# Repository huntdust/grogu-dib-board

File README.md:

# grogu-dib-board
 DIB board for Grogu PTL

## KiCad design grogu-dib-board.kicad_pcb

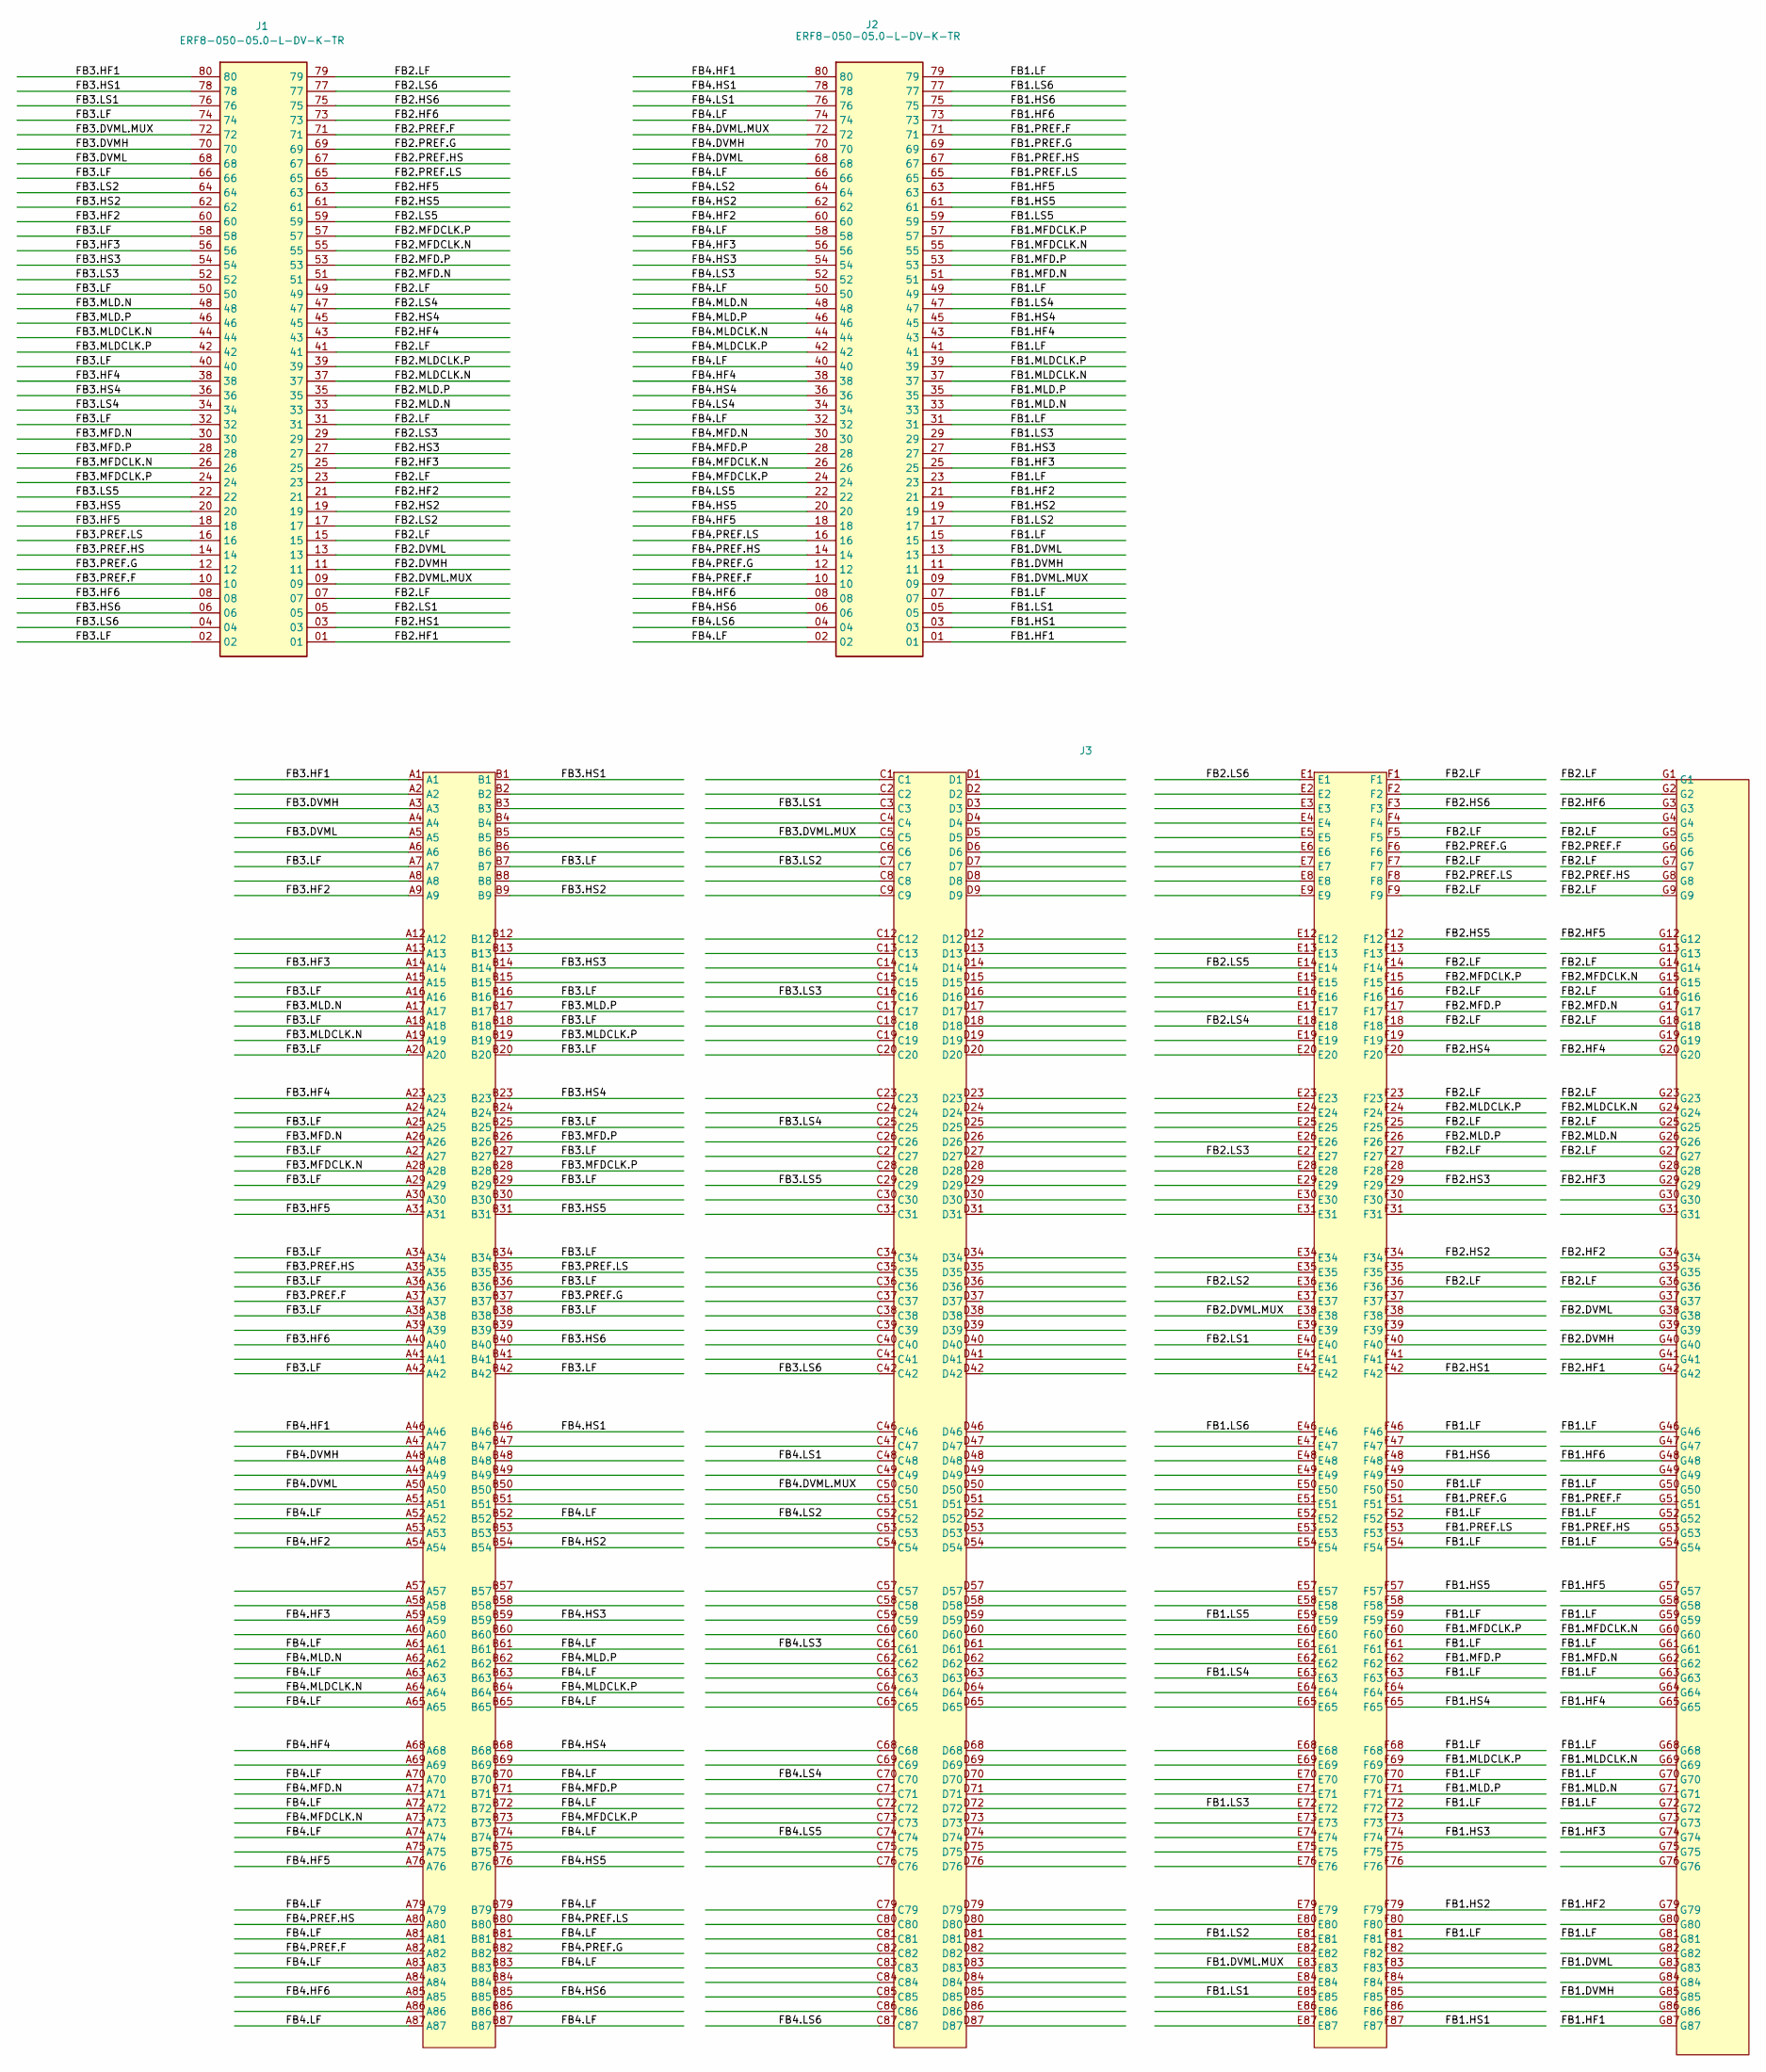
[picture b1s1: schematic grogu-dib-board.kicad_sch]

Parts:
J1, J2: ERF8-050-05.0-L-DV-K-TR; SAMTEC_ERF8-040-05.0-L-DV-K-TR; Mouser Part Number 200-ERF8050050LDVKTR
J3: Grogu-dib-topcu-mirror-secondary-side

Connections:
/FB1.DVMH: J2.11, J3.G85
/FB1.DVML: J2.13, J3.G83
/FB1.DVML.MUX: J2.09, J3.E83
/FB1.HF1: J2.01, J3.G87
/FB1.HF2: J2.21, J3.G79
/FB1.HF3: J2.25, J3.G74
/FB1.HF4: J2.43, J3.G65
/FB1.HF5: J2.63, J3.G57
/FB1.HF6: J2.73, J3.G48
/FB1.HS1: J2.03, J3.F87
/FB1.HS2: J2.19, J3.F79
/FB1.HS3: J2.27, J3.F74
/FB1.HS4: J2.45, J3.F65
/FB1.HS5: J2.61, J3.F57
/FB1.HS6: J2.75, J3.F48
/FB1.LF: J2.07, J2.15, J2.23, J2.31, J2.41, J2.49, J2.79, J3.F46, J3.F50, J3.F52, J3.F54, J3.F59, J3.F61, J3.F63, J3.F68, J3.F70, J3.F72, J3.F81, J3.G46, J3.G50, J3.G52, J3.G54, J3.G59, J3.G61, J3.G63, J3.G68, J3.G70, J3.G72, J3.G81
/FB1.LS1: J2.05, J3.E85
/FB1.LS2: J2.17, J3.E81
/FB1.LS3: J2.29, J3.E72
/FB1.LS4: J2.47, J3.E63
/FB1.LS5: J2.59, J3.E59
/FB1.LS6: J2.77, J3.E46
/FB1.MFD.N: J2.51, J3.G62
/FB1.MFD.P: J2.53, J3.F62
/FB1.MFDCLK.N: J2.55, J3.G60
/FB1.MFDCLK.P: J2.57, J3.F60
/FB1.MLD.N: J2.33, J3.G71
/FB1.MLD.P: J2.35, J3.F71
/FB1.MLDCLK.N: J2.37, J3.G69
/FB1.MLDCLK.P: J2.39, J3.F69
/FB1.PREF.F: J2.71, J3.G51
/FB1.PREF.G: J2.69, J3.F51
/FB1.PREF.HS: J2.67, J3.G53
/FB1.PREF.LS: J2.65, J3.F53
/FB2.DVMH: J1.11, J3.G40
/FB2.DVML: J1.13, J3.G38
/FB2.DVML.MUX: J1.09, J3.E38
/FB2.HF1: J1.01, J3.G42
/FB2.HF2: J1.21, J3.G34
/FB2.HF3: J1.25, J3.G29
/FB2.HF4: J1.43, J3.G20
/FB2.HF5: J1.63, J3.G12
/FB2.HF6: J1.73, J3.G3
/FB2.HS1: J1.03, J3.F42
/FB2.HS2: J1.19, J3.F34
/FB2.HS3: J1.27, J3.F29
/FB2.HS4: J1.45, J3.F20
/FB2.HS5: J1.61, J3.F12
/FB2.HS6: J1.75, J3.F3
/FB2.LF: J1.07, J1.15, J1.23, J1.31, J1.41, J1.49, J1.79, J3.F1, J3.F5, J3.F7, J3.F9, J3.F14, J3.F16, J3.F18, J3.F23, J3.F25, J3.F27, J3.F36, J3.G1, J3.G5, J3.G7, J3.G9, J3.G14, J3.G16, J3.G18, J3.G23, J3.G25, J3.G27, J3.G36
/FB2.LS1: J1.05, J3.E40
/FB2.LS2: J1.17, J3.E36
/FB2.LS3: J1.29, J3.E27
/FB2.LS4: J1.47, J3.E18
/FB2.LS5: J1.59, J3.E14
/FB2.LS6: J1.77, J3.E1
/FB2.MFD.N: J1.51, J3.G17
/FB2.MFD.P: J1.53, J3.F17
/FB2.MFDCLK.N: J1.55, J3.G15
/FB2.MFDCLK.P: J1.57, J3.F15
/FB2.MLD.N: J1.33, J3.G26
/FB2.MLD.P: J1.35, J3.F26
/FB2.MLDCLK.N: J1.37, J3.G24
/FB2.MLDCLK.P: J1.39, J3.F24
/FB2.PREF.F: J1.71, J3.G6
/FB2.PREF.G: J1.69, J3.F6
/FB2.PREF.HS: J1.67, J3.G8
/FB2.PREF.LS: J1.65, J3.F8
/FB3.DVMH: J1.70, J3.A3
/FB3.DVML: J1.68, J3.A5
/FB3.DVML.MUX: J1.72, J3.C5
/FB3.HF1: J1.80, J3.A1
/FB3.HF2: J1.60, J3.A9
/FB3.HF3: J1.56, J3.A14
/FB3.HF4: J1.38, J3.A23
/FB3.HF5: J1.18, J3.A31
/FB3.HF6: J1.08, J3.A40
/FB3.HS1: J1.78, J3.B1
/FB3.HS2: J1.62, J3.B9
/FB3.HS3: J1.54, J3.B14
/FB3.HS4: J1.36, J3.B23
/FB3.HS5: J1.20, J3.B31
/FB3.HS6: J1.06, J3.B40
/FB3.LF: J1.02, J1.32, J1.40, J1.50, J1.58, J1.66, J1.74, J3.A7, J3.A16, J3.A18, J3.A20, J3.A25, J3.A27, J3.A29, J3.A34, J3.A36, J3.A38, J3.A42, J3.B7, J3.B16, J3.B18, J3.B20, J3.B25, J3.B27, J3.B29, J3.B34, J3.B36, J3.B38, J3.B42
/FB3.LS1: J1.76, J3.C3
/FB3.LS2: J1.64, J3.C7
/FB3.LS3: J1.52, J3.C16
/FB3.LS4: J1.34, J3.C25
/FB3.LS5: J1.22, J3.C29
/FB3.LS6: J1.04, J3.C42
/FB3.MFD.N: J1.30, J3.A26
/FB3.MFD.P: J1.28, J3.B26
/FB3.MFDCLK.N: J1.26, J3.A28
/FB3.MFDCLK.P: J1.24, J3.B28
/FB3.MLD.N: J1.48, J3.A17
/FB3.MLD.P: J1.46, J3.B17
/FB3.MLDCLK.N: J1.44, J3.A19
/FB3.MLDCLK.P: J1.42, J3.B19
/FB3.PREF.F: J1.10, J3.A37
/FB3.PREF.G: J1.12, J3.B37
/FB3.PREF.HS: J1.14, J3.A35
/FB3.PREF.LS: J1.16, J3.B35
/FB4.DVMH: J2.70, J3.A48
/FB4.DVML: J2.68, J3.A50
/FB4.DVML.MUX: J2.72, J3.C50
/FB4.HF1: J2.80, J3.A46
/FB4.HF2: J2.60, J3.A54
/FB4.HF3: J2.56, J3.A59
/FB4.HF4: J2.38, J3.A68
/FB4.HF5: J2.18, J3.A76
/FB4.HF6: J2.08, J3.A85
/FB4.HS1: J2.78, J3.B46
/FB4.HS2: J2.62, J3.B54
/FB4.HS3: J2.54, J3.B59
/FB4.HS4: J2.36, J3.B68
/FB4.HS5: J2.20, J3.B76
/FB4.HS6: J2.06, J3.B85
/FB4.LF: J2.02, J2.32, J2.40, J2.50, J2.58, J2.66, J2.74, J3.A52, J3.A61, J3.A63, J3.A65, J3.A70, J3.A72, J3.A74, J3.A79, J3.A81, J3.A83, J3.A87, J3.B52, J3.B61, J3.B63, J3.B65, J3.B70, J3.B72, J3.B74, J3.B79, J3.B81, J3.B83, J3.B87
/FB4.LS1: J2.76, J3.C48
/FB4.LS2: J2.64, J3.C52
/FB4.LS3: J2.52, J3.C61
/FB4.LS4: J2.34, J3.C70
/FB4.LS5: J2.22, J3.C74
/FB4.LS6: J2.04, J3.C87
/FB4.MFD.N: J2.30, J3.A71
/FB4.MFD.P: J2.28, J3.B71
/FB4.MFDCLK.N: J2.26, J3.A73
/FB4.MFDCLK.P: J2.24, J3.B73
/FB4.MLD.N: J2.48, J3.A62
/FB4.MLD.P: J2.46, J3.B62
/FB4.MLDCLK.N: J2.44, J3.A64
/FB4.MLDCLK.P: J2.42, J3.B64
/FB4.PREF.F: J2.10, J3.A82
/FB4.PREF.G: J2.12, J3.B82
/FB4.PREF.HS: J2.14, J3.A80
/FB4.PREF.LS: J2.16, J3.B80

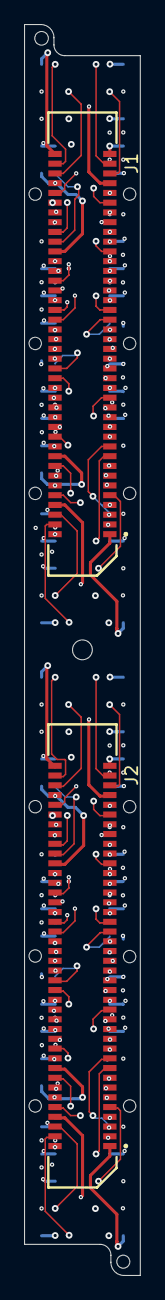
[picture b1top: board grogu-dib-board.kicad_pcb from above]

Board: 4 copper layers, 9.5 x 102.6 mm, 14 parts (1 on the bottom side), 136 nets.

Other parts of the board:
1, 2, 3, 4, 5, 6, 7, 8, 9, 10, 11: (no value)

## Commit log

2024-07-15 First commit - prior to implementing summit changes
    Mockup#1 prior to making requested changes from Summit Interconnect
2024-07-15 Summit Modifications
    - Removed pads where connector hole emerges on bottom side
    - Re-routed traces to avoid counterbore
    - Soldermask clearance increased on bottom side for counterbore
    - Removed stackup table (2mm thickness per summit quote)
2024-07-15 Fabrication Outputs for Summit Revisions
2024-07-18 schematic done
2024-08-05 first pass routing
2024-08-05 new route
2024-08-07 routing update
2024-08-07 more routing
2024-08-08 layout done
2024-08-09 final design
2024-08-09 final_w_updated_vias
2024-08-09 fix 1-3 vias
